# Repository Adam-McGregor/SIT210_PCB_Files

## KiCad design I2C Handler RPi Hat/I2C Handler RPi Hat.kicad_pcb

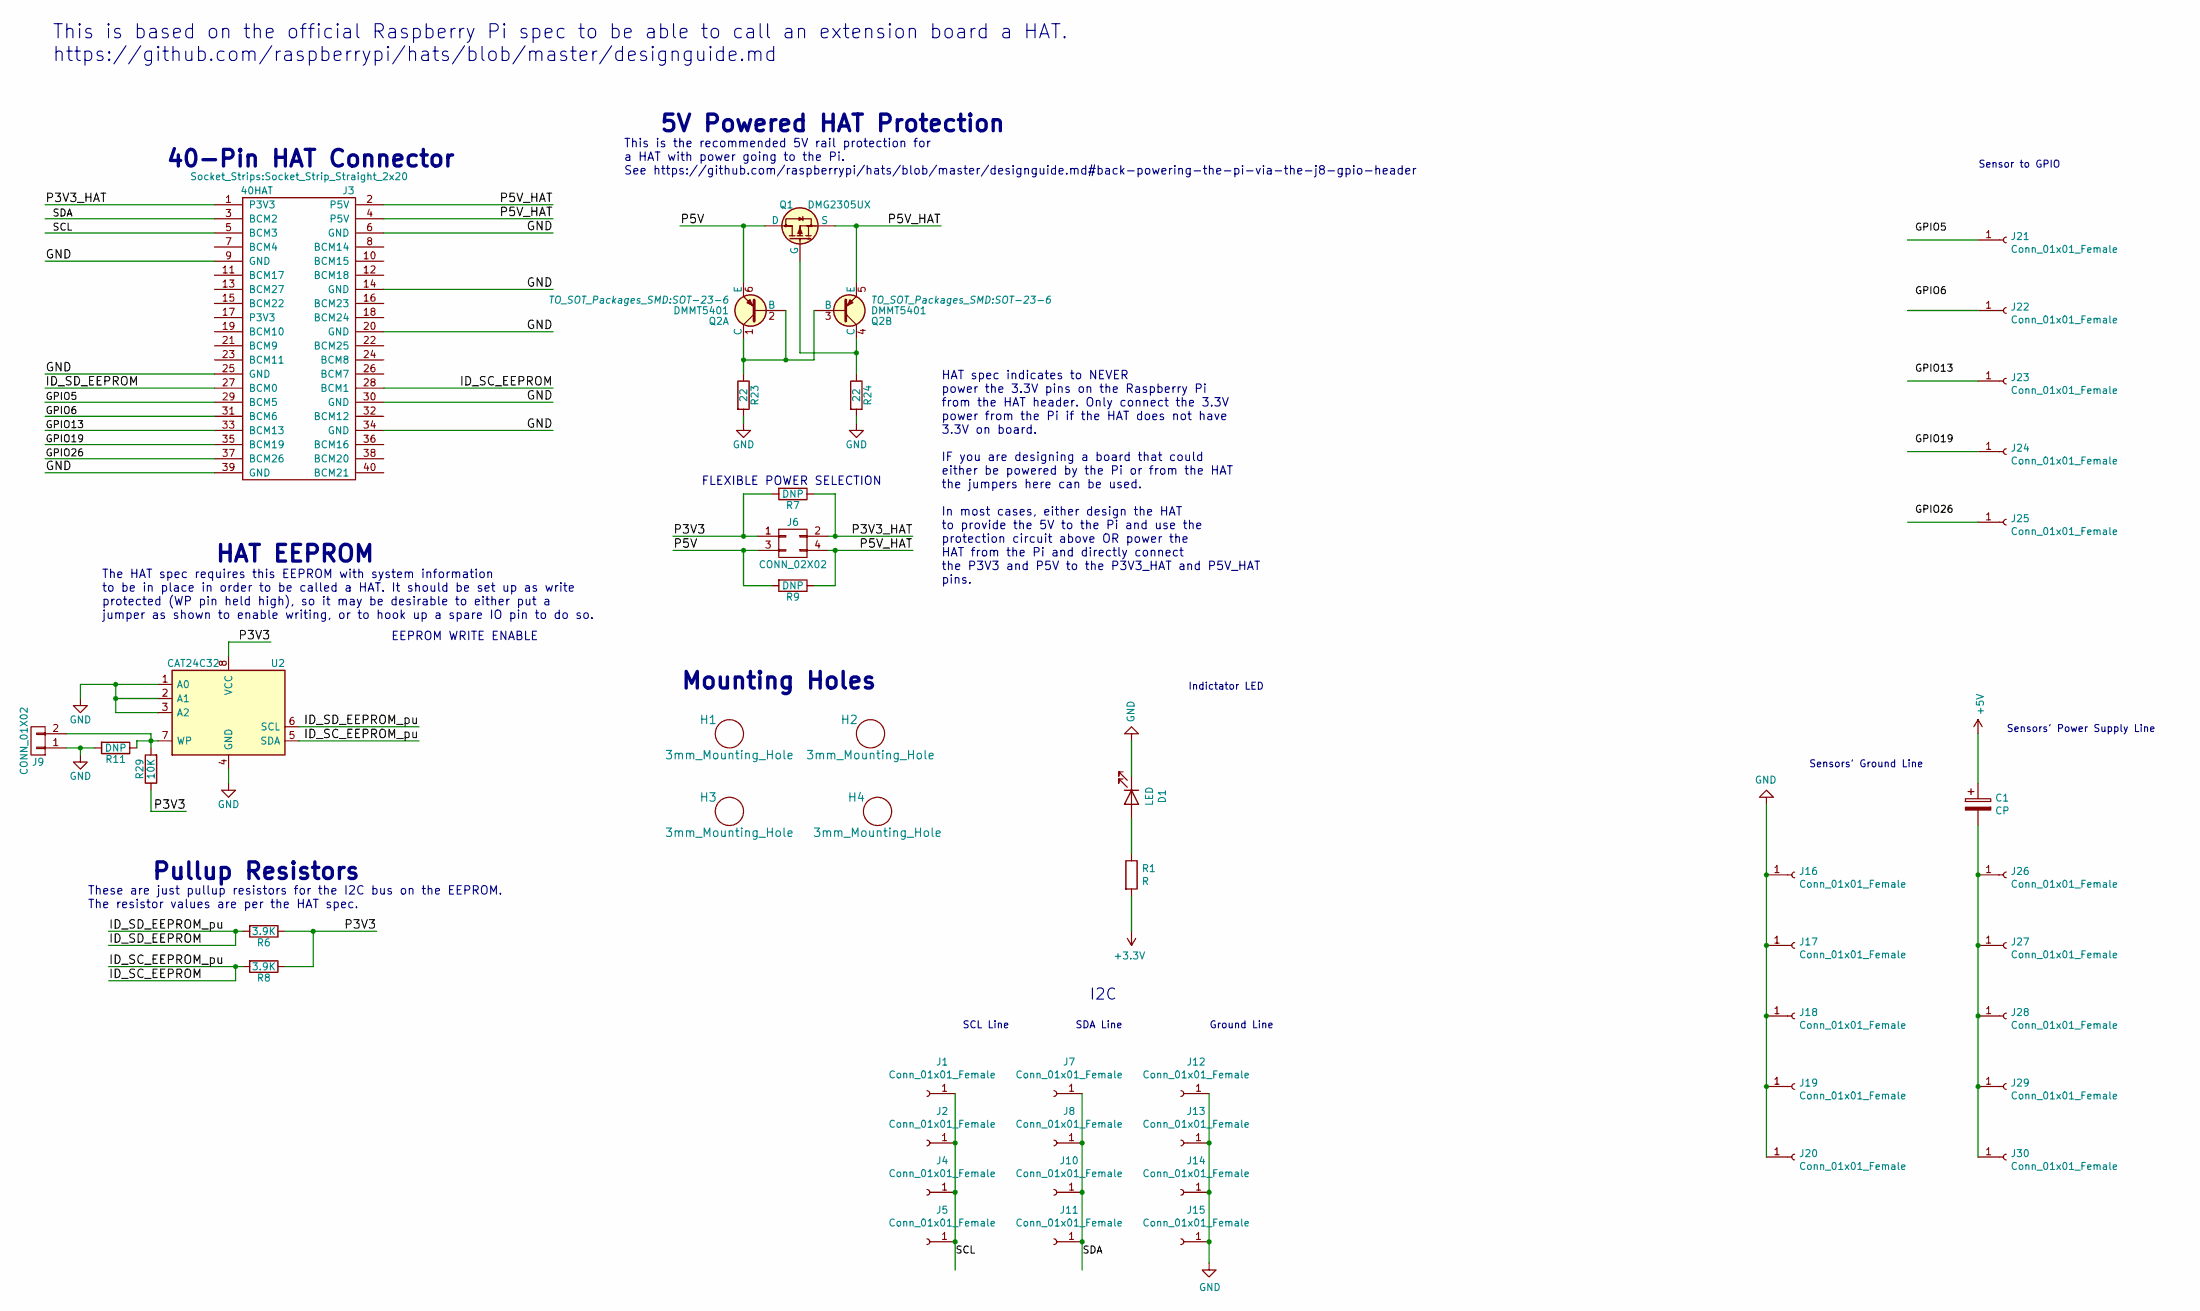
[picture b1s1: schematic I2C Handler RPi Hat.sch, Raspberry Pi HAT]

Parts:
C1: CP; CP_Axial_L10.0mm_D4.5mm_P15.00mm_Horizontal
D1: LED; LED_D1.8mm_W1.8mm_H2.4mm_Horizontal_O1.27mm_Z1.6mm
H1, H2, H3, H4: 3mm_Mounting_Hole; NPTH_3mm_ID
J1, J2, J4, J5, J7, J8, J10, J11, J12, J13, J14, J15, J16, J17, J18, J19, J20, J21, J22, J23, J24, J25, J26, J27, J28, J29, J30: Conn_01x01_Female; Pin_D0.7mm_L6.5mm_W1.8mm_FlatFork
J3: 40HAT; Socket_Strip_Straight_2x20
J6: CONN_02X02; Pin_Header_Straight_2x02
J9: CONN_01X02; Pin_Header_Straight_1x02
Q1: DMG2305UX; SOT-23
Q2: DMMT5401; SOT-23-6
R1: R; R_0201_0603Metric
R6, R8: 3.9K; R_0603_HandSoldering; MPN RC0402JR-0722RL
R7, R9, R11: DNP; R_0805_HandSoldering; MPN RC0402JR-0722RL
R23, R24: 22; R_0603_HandSoldering; MPN RC0402JR-0722RL
R29: 10K; R_0603_HandSoldering; MPN RC0402JR-0722RL
U2: CAT24C32; SOIC-8_3.9x4.9mm_Pitch1.27mm

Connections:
+3V3: R1.2
+5V: C1.1
/GPIO5: J3.29 (BCM5)
/GPIO6: J3.31 (BCM6)
/GPIO13: J3.33 (BCM13)
/GPIO19: J3.35 (BCM19)
/GPIO26: J3.37 (BCM26)
/ID_SC_EEPROM: J3.28 (BCM1), R8.2, U2.5 (SDA)
/ID_SD_EEPROM: J3.27 (BCM0), R6.2, U2.6 (SCL)
/P3V3: J6.1, R6.1, R7.2, R8.1, R29.1, U2.8 (VCC)
/P3V3_HAT: J3.1 (P3V3), J6.2, R7.1
/P5V: J6.3, Q1.3 (D), Q2.6 (E), R9.2
/P5V_HAT: J3.2 (P5V), J3.4 (P5V), J6.4, Q1.2 (S), Q2.5 (E), R9.1
/SCL: J1.1, J2.1, J3.5 (BCM3), J4.1, J5.1
/SDA: J3.3 (BCM2), J7.1, J8.1, J10.1, J11.1
GND: D1.1 (K), J3.6 (GND), J3.9 (GND), J3.14 (GND), J3.20 (GND), J3.25 (GND), J3.30 (GND), J3.34 (GND), J3.39 (GND), J9.1, J12.1, J13.1, J14.1, J15.1, J16.1, J17.1, J18.1, J19.1, J20.1, R11.2, R23.2, R24.2, U2.1 (A0), U2.2 (A1), U2.3 (A2), U2.4 (GND)
unnamed: C1.2, J26.1, J27.1, J28.1, J29.1, J30.1
unnamed: D1.2 (A), R1.1
unnamed: J9.2, R11.1, R29.2, U2.7 (WP)
unnamed: Q1.1 (G), Q2.4 (C), R24.1
unnamed: Q2.1 (C), Q2.2 (B), Q2.3 (B), R23.1

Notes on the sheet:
FLEXIBLE POWER SELECTION
5V Powered HAT Protection
This is the recommended 5V rail protection for a HAT with power going to the Pi. See https://github.com/raspberrypi/hats/blob/master/designguide.md#back-powering-the-pi-via-the-j8-gpio-header
EEPROM WRITE ENABLE
Pullup Resistors
HAT EEPROM
Mounting Holes
40-Pin HAT Connector
HAT spec indicates to NEVER power the 3.3V pins on the Raspberry Pi from the HAT header. Only connect the 3.3V power from the Pi if the HAT does not have 3.3V on board. IF you are designing a board that could either be powered by the Pi or from the HAT the jumpers here can be used. In most cases, e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
The HAT spec requires this EEPROM with system information to be in place in order to be called a HAT. It should be set up as write protected (WP pin held high), so it may be desirable to either put a jumper as shown to enable writing, or to hook up a spare IO pin to do so.
These are just pullup resistors for the I2C bus on the EEPROM. The resistor values are per the HAT spec.
This is based on the official Raspberry Pi spec to be able to call an extension board a HAT. https://github.com/raspberrypi/hats/blob/master/designguide.md
Indictator LED
Ground Line
Sensors' Power Supply Line
Sensors' Ground Line
I2C
SCL Line
SDA Line
Sensor to GPIO

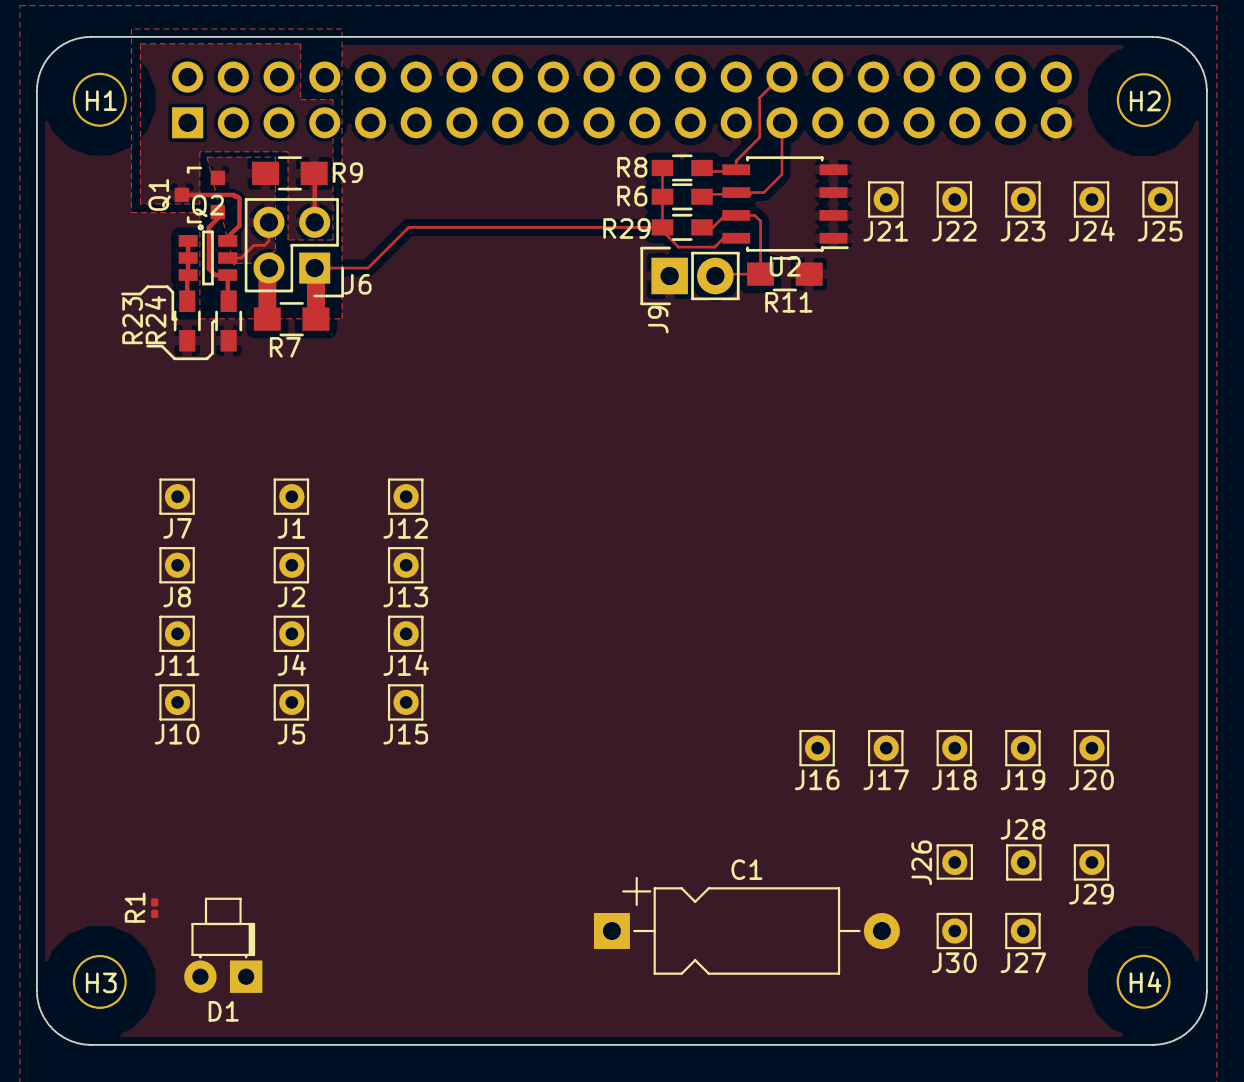
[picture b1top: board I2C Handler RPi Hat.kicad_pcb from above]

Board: 4 copper layers, 65.0 x 56.0 mm, 48 parts (1 on the bottom side), 14 nets.
